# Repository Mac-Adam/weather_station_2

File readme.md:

## 3D Printable weather station

This is the repository for my personal project, a weather station.
It is based on ESP32. You can view the source code in the weather station folder.
All the 3d models are available in the 3d models folder.
Folder old has the program for an older version of the design.
Folder tests has a few programs created to calibrate or test individual components.
The stations has following functionality:

- Temperature, humidity and pressure sensor
- Air quality sensor
- Custom wind speed meter
- Custom wind direction meter
- Custom rain meter with heating to measure snow

## Building And Running

Open the Weather_station project in arudino studio and program your ESP32.
Before programing, create a secrets.ino file:

```

#ifndef SECRETS

#define WIFINAME "Name of your WiFi"
#define PASSWORD "Your WiFi Password"
#define ID Unique ID
#define SERVERNAME "Url for your server"
#else

#define SECRETS
#endif
```

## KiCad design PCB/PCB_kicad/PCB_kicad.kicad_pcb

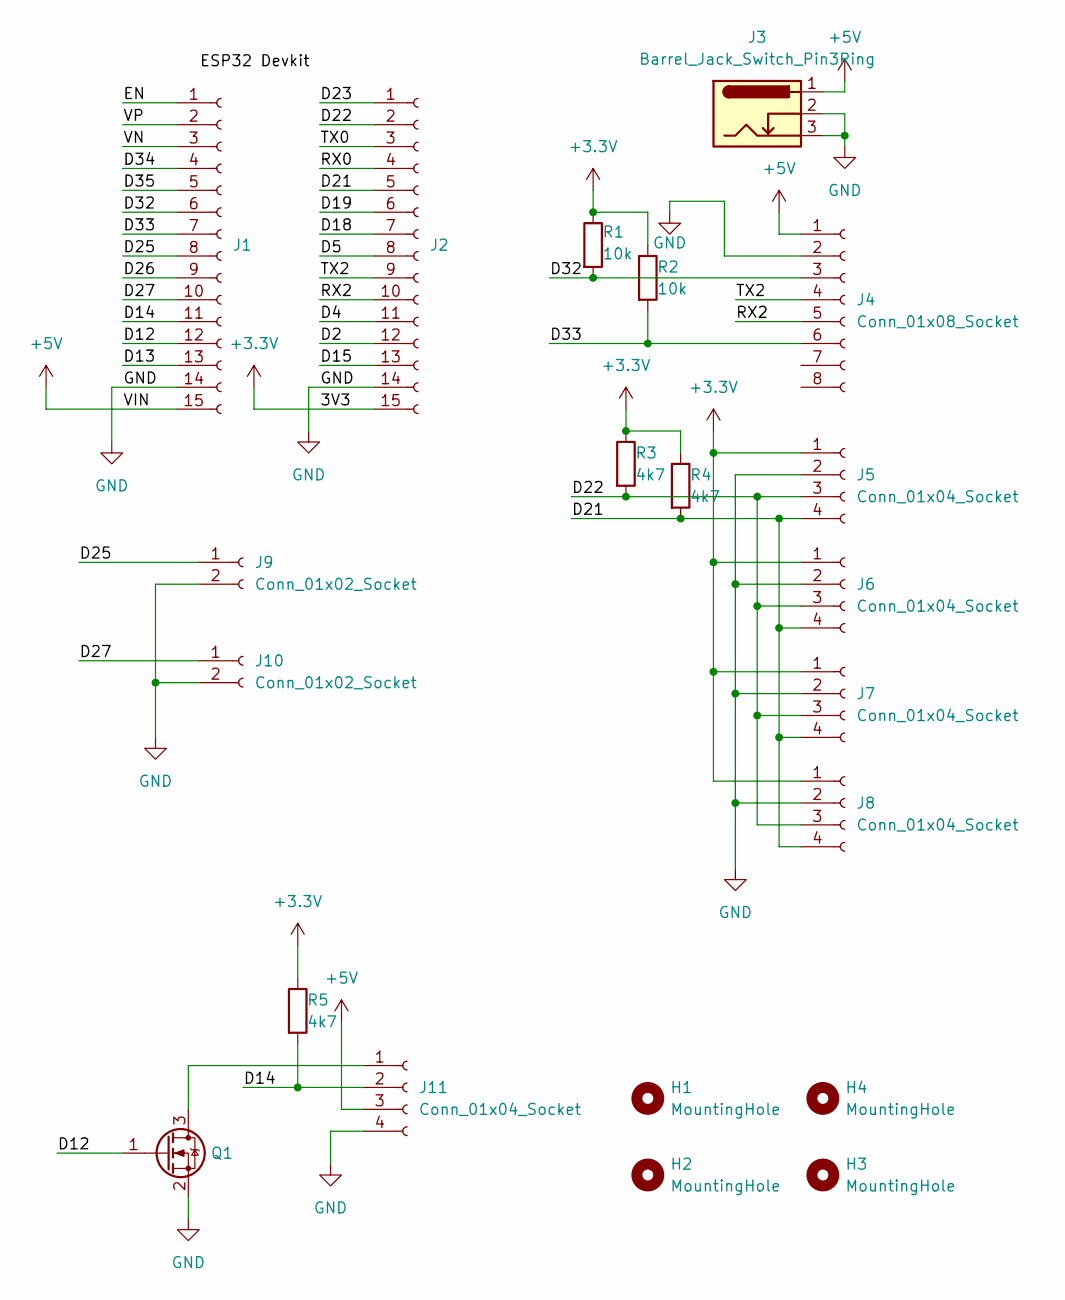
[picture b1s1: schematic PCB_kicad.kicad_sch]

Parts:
H1, H2, H3, H4: MountingHole; MountingHole_3.2mm_M3
J1, J2: Conn_01x15_Socket; PinHeader_1x15_P2.54mm_Vertical
J3: Barrel_Jack_Switch_Pin3Ring; BarrelJack_Horizontal
J4: Conn_01x08_Socket; Molex_PicoBlade_53047-0810_1x08_P1.25mm_Vertical
J5, J6, J7, J8, J11: Conn_01x04_Socket; PinHeader_1x04_P2.54mm_Vertical
J9, J10: Conn_01x02_Socket; PinHeader_1x02_P2.54mm_Vertical
Q1: 2N7002; SOT-23
R1, R2: 10k; R_Axial_DIN0204_L3.6mm_D1.6mm_P7.62mm_Horizontal
R3, R4, R5: 4k7; R_Axial_DIN0204_L3.6mm_D1.6mm_P7.62mm_Horizontal

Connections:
+3.3V: J2.15, J5.1, J6.1, J7.1, J8.1, R1.1, R2.1, R3.1, R4.1, R5.1
+5V: J1.15, J3.1, J4.1, J11.3
/D2: J2.12
/D4: J2.11
/D5: J2.8
/D12: J1.12, Q1.1 (G)
/D13: J1.13
/D14: J1.11, J11.2, R5.2
/D15: J2.13
/D18: J2.7
/D19: J2.6
/D21: J2.5, J5.4, J6.4, J7.4, J8.4, R4.2
/D22: J2.2, J5.3, J6.3, J7.3, J8.3, R3.2
/D23: J2.1
/D25: J1.8, J9.1
/D26: J1.9
/D27: J1.10, J10.1
/D32: J1.6, J4.3, R1.2
/D33: J1.7, J4.6, R2.2
/D34: J1.4
/D35: J1.5
/EN: J1.1
/RX0: J2.4
/RX2: J2.10, J4.5
/TX0: J2.3
/TX2: J2.9, J4.4
/VN: J1.3
/VP: J1.2
GND: J1.14, J2.14, J3.2, J3.3, J4.2, J5.2, J6.2, J7.2, J8.2, J9.2, J10.2, J11.4, Q1.2 (S)
unnamed: J11.1, Q1.3 (D)

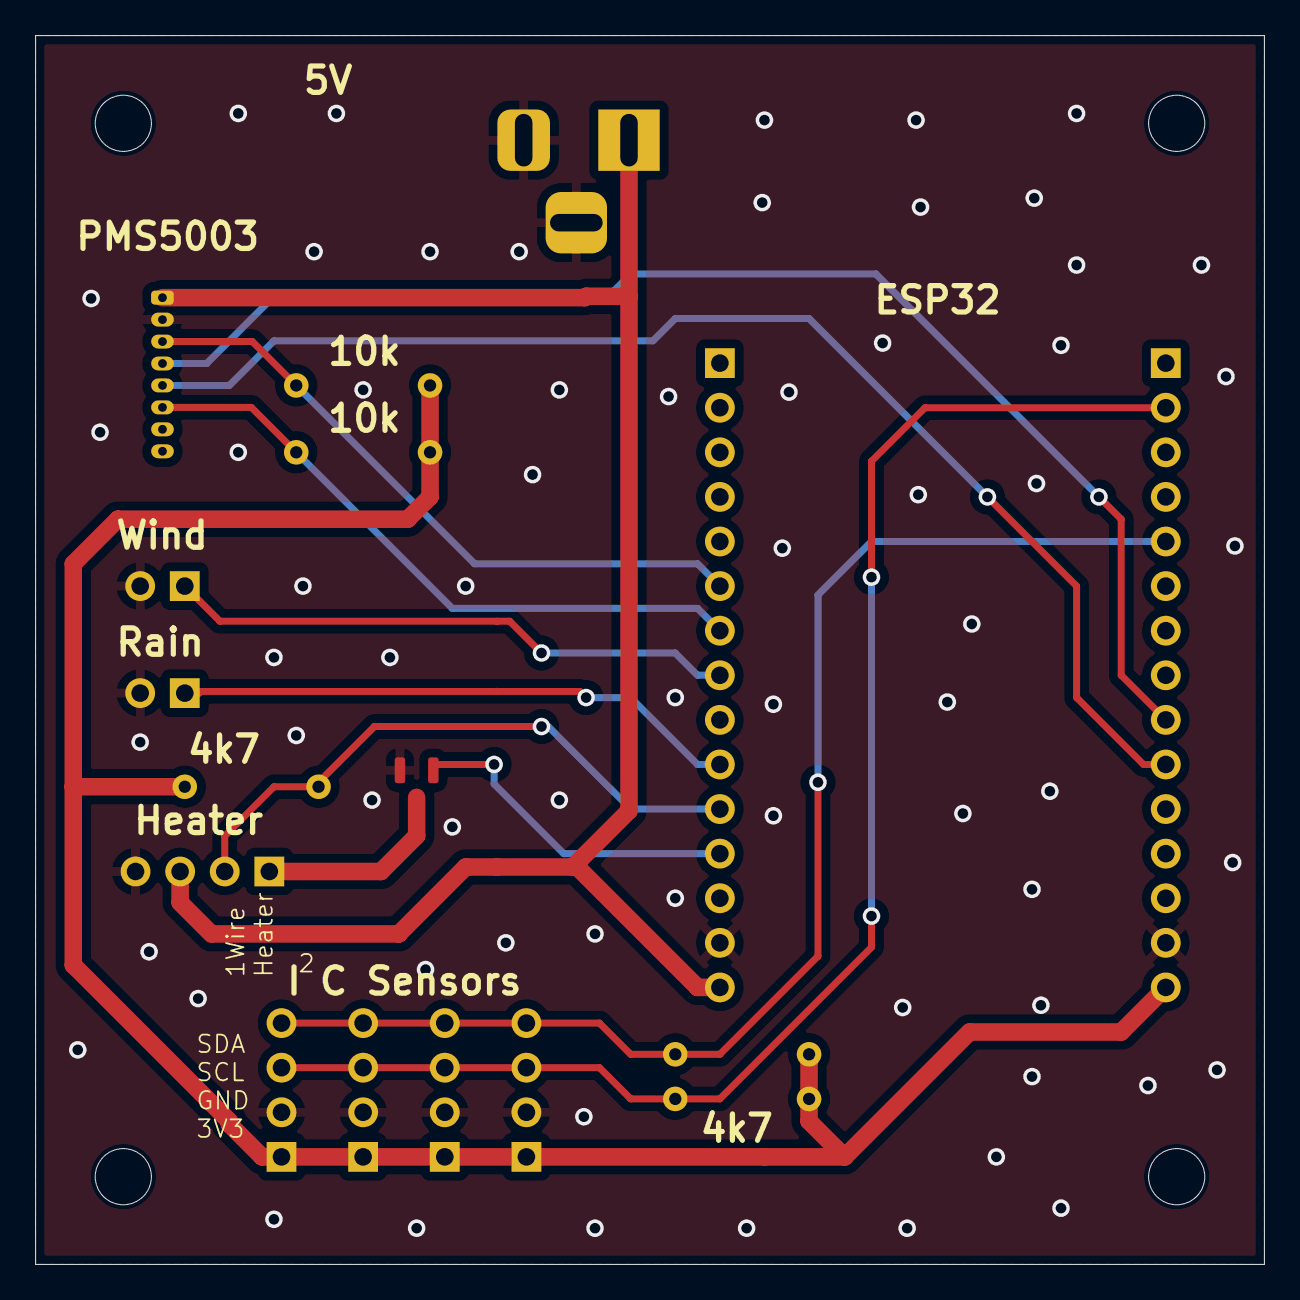
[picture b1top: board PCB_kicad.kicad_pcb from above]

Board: 2 copper layers, 70.0 x 70.0 mm, 21 parts (0 on the bottom side), 14 nets.

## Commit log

2025-01-31 Initial commit
    This is all the code form the private repo but with secret data removed
2025-02-05 3d models
2025-02-05 basic readme
2025-12-02 New PCB
2026-03-01 Improved stability
    Added some minor tweaks to improve the stability of the desing
